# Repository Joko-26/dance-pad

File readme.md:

# My first PCB ever

## Table of contents

- [project description](#project-description)
- [project structure](#project-structure)
- [pins](#pins)
- [Bom](#bom)
- [case](#case)
- [shematic](#shematic)
- [gallery](#gallery)

---

## Project description

This is a figetoy style mini game board with space for up to 6 operating modes thanks to a 6 pos rotary switch. It features 4 keyboard switches for user interaction, 4 different colored leds corresponding to the 4 buttons and a sigular led for status messages (win, loose...) 

## Project structure

The repository and project is organized into themed folders:

folder | contents
--- | ---
`/screenshots` | various images of the project
`/pcb` | kicad source files
`/gerbers` | gerber files neccesary for pcb production
`/code` | code files
`/cad` | .3mf and source files for the 3d printable case
`/dancePad` | repository files
`/manufacturing` | containes .step files for manufacturing

## pins

pin|designation
---|---
7|led left
6|led right
4|led top
5|led bottom
1|button left
3|button right
9|button top
2|button bottom
9|special led
0|6 position rotary (values WIP)

## Bom

## case

The case is fully 3d printable with the exeption of 4 3Mx6 screws.

## shematic

## gallery

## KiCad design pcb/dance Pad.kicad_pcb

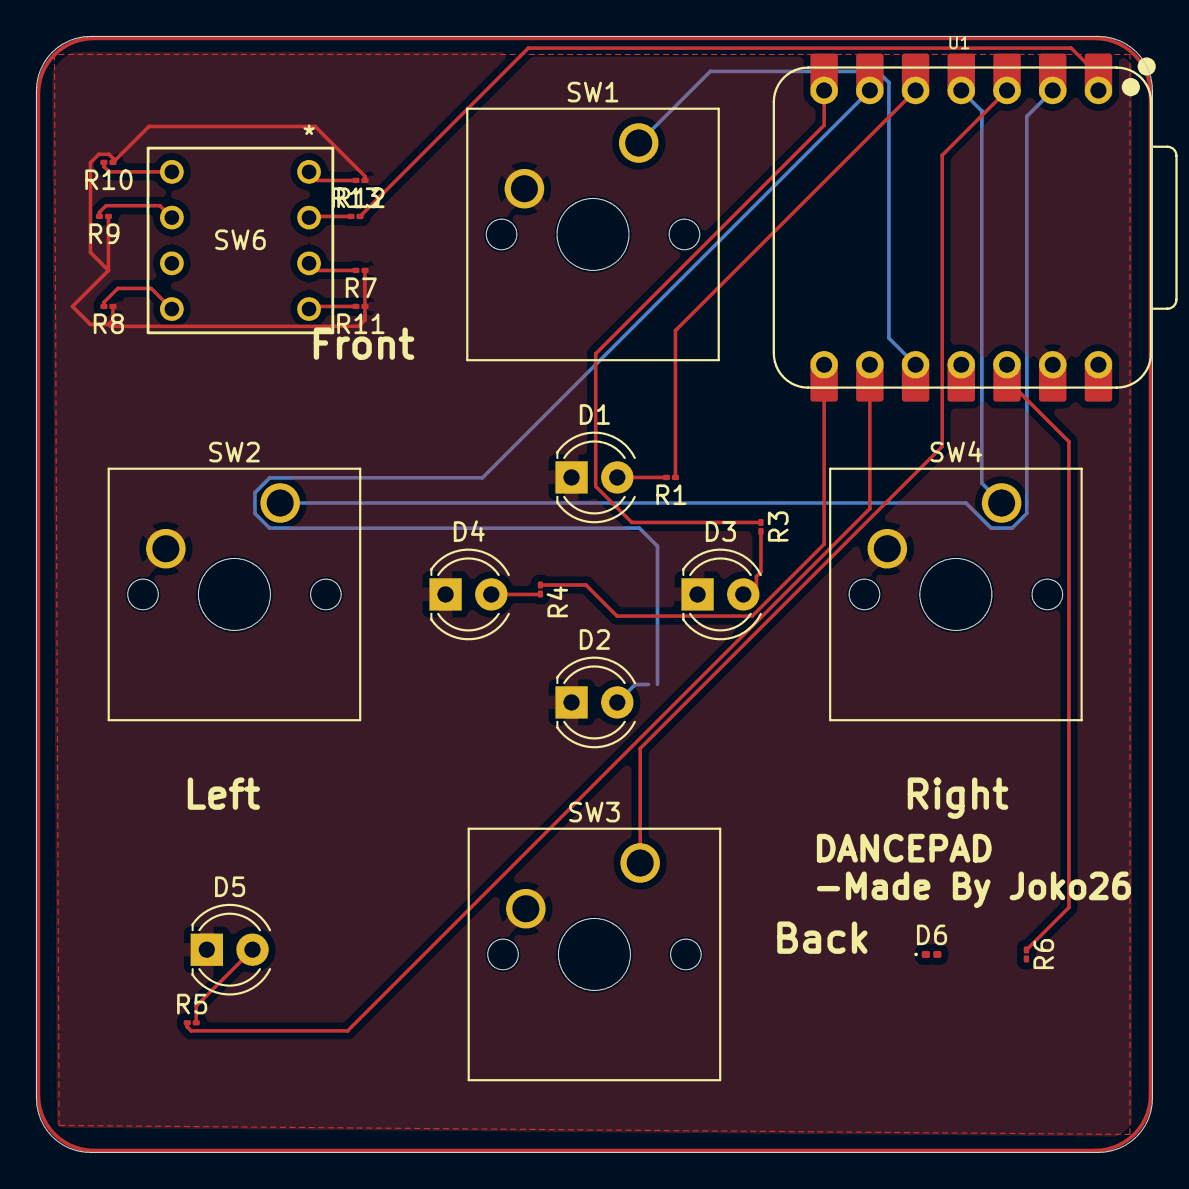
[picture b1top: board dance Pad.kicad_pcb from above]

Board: 2 copper layers, 62.0 x 62.0 mm, 25 parts (1 on the bottom side), 23 nets.

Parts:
D1, D2, D3, D4, D5: LED; LED_D4.0mm
D6: Status LED; LED_0201_0603Metric
R1, R2, R3, R4, R5, R6: 220; R_01005_0402Metric
R7: 1k; R_01005_0402Metric
R8: 2k; R_01005_0402Metric
R9: 4k; R_01005_0402Metric
R10: 8k; R_01005_0402Metric
R11: 16k; R_01005_0402Metric
R12: 32k; R_01005_0402Metric
R13: 10k; R_01005_0402Metric
SW1, SW2, SW3, SW4: SW_Push; SW_Cherry_MX_1.00u_PCB
SW6: SS-10-16SP-L-AE; SS-10-16SP_NDC
U1: XIAO-Add-On; XIAO-RP2040-DIP

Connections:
GND: D1.1 (K), D2.1 (K), D3.1 (K), D4.1 (K), D5.1 (K), R7.1, R8.1, R9.1, R10.1, R11.1, R12.1, SW1.2, SW2.2, SW3.2, SW4.2, U1.13 (GND)
unnamed: D1.2 (A), R1.2
unnamed: D2.2 (A), R2.2
unnamed: D3.2 (A), R3.2
unnamed: D4.2 (A), R4.2
unnamed: D5.2 (A), R5.2
unnamed: D6.2 (A_2), R6.2
unnamed: R12.2, SW6.1
unnamed: R11.2, SW6.3 (2)
unnamed: R10.2, SW6.4 (3)
unnamed: R9.2, SW6.5 (4)
unnamed: R8.2, SW6.6 (5)
unnamed: R6.1, U1.12 (3V3_OUT)
unnamed: R13.2, U1.1 (D0)
unnamed: SW2.1, U1.2 (D1)
unnamed: SW3.1, U1.3 (D2)
unnamed: SW4.1, U1.4 (D3)
unnamed: R1.1, U1.5 (D4)
unnamed: R2.1, U1.6 (D5)
unnamed: R3.1, U1.7 (D6)
unnamed: R4.1, U1.8 (D7)
unnamed: R5.1, U1.9 (D8)
unnamed: SW1.1, U1.10 (D9)
